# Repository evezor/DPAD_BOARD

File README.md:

# Evezor Potentiometer Board

*please note this board is has been deprecated.

This board uses the Evezor Stamp STMF405 MCU

source: https://github.com/evezor/Evezor-Stamp-STMF405

An Edge boad with two buttons, two potentiometers and 2 multiplexed led bar graphs

Evezor® and all associated marks, logos, and designs are registered trademarks and protected by copyright. Unauthorized use or reproduction of these trademarks and copyrighted materials is strictly prohibited

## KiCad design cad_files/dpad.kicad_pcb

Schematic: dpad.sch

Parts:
C1, C3: .1uF 100V; C_0805_2012Metric
C2, C5, C9, C10, C14: .1uF; C_0603_1608Metric
C4: 4.7uF; C_0805_2012Metric
C6, C7, C11, C13, C15: 22uF; C_0805_2012Metric
D1, D2: SX35_SCHOTTKY; D_SMA
D3, D4, D5, D8, D9, D10: LED; LED_0603_1608Metric
D6: SK6812MINI; LED_SK6812MINI_PLCC4_3.5x3.5mm_P1.75mm
D7: D_TVS_x2_AAC; SOT-23
J2: ftdi_conn; CONN-SH-6P-VERTICAL
J3: Conn_01x02; BOOT_JUMPER
J4, J5: Conn_01x04; JST_PH_S4B-PH-SM4-TB_1x04-1MP_P2.00mm_Horizontal
L1: 22uH; INDUCTOR_7.5X6.6_GCDA0630-220MC
R1, R3, R4, R6, R8, R9, R10: 10k; R_0603_1608Metric
R2: 82k; R_0603_1608Metric
R5, R7: 15k; R_0603_1608Metric
SW1, SW2, SW3, SW4: SW_Push; SWITCH_2x3_SMD_TACTILE_GREEN
U1: SY8401ABC; SOT-23-6
U2: AMS1117-3.3; SOT-223-3_TabPin2
U3: ESP32-WROOM-32U
U4: SWITCH_5-WAY_TACTIL_10X10; SWITCH_5WAY_10x10
U5: Trans_CAN_SN65HVD230DR; CAN-TRANS-SN65HVD230DR

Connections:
+3V3: C7.1, C9.2, C10.1, C11.1, C13.1, C14.1, C15.1, D6.4 (VDD), R3.2, R6.2, U2.2 (VO), U3.2, U5.3
/BOOT: J2.4, J3.1, U3.25
/BUTTON_A: SW4.1, U3.37
/BUTTON_B: SW3.1, U3.36
/CAN_H: D7.2, J4.2, J5.2, U5.7
/CAN_L: D7.1, J4.1, J5.1, U5.6
/CAN_RX: U3.27, U5.4
/CAN_SLP: U3.24, U5.8
/CAN_TX: U3.26, U5.1
/DPAD_DOWN: U3.12, U4.6
/DPAD_LEFT: U3.9, U4.2
/DPAD_PUSH: U3.8, U4.3
/DPAD_RIGHT: U3.11, U4.5
/DPAD_UP: U3.10, U4.4
/FUNCTION_BUTTON: R3.1, SW1.1, U3.4
/HBT_LED: D3.2 (A), U3.29
/LED_0: R4.2, U3.23
/LED_1: R8.2, U3.30
/LED_2: R9.2, U3.31
/LED_3: R10.2, U3.33
/NEO_STATUS: D6.3 (DIN), U3.28
/PWR: C3.1, C4.1, D2.1 (K), D8.2 (A), U1.4 (EN), U1.5 (VIN)
/RESET: J2.1, R6.1, SW2.1, U3.3
/RXD0: J2.3, U3.34
/TXDO: J2.2, U3.35
/VREG_OUT: C2.1, C5.1, C6.1, L1.2, R2.1, U2.3 (VI)
GND: C3.2, C4.2, C5.2, C6.2, C7.2, C9.1, C10.2, C11.2, C13.2, C14.2, C15.2, D1.2 (A), D4.1 (K), D5.1 (K), D6.2 (VSS), D7.3, D9.1 (K), D10.1 (K), J2.6, J3.2, J4.4, J5.4, R1.1, R5.1, R7.1, SW1.2, SW2.2, SW3.2, SW4.2, U1.2 (GND), U2.1 (GND), U3.1, U3.15, U3.38, U3.39, U4.1, U5.2
unnamed: C1.1, D1.1 (K), L1.1, U1.6 (SW)
unnamed: C1.2, U1.1 (CB)
unnamed: C2.2, R1.2, R2.2, U1.3 (FB)
unnamed: D3.1 (K), R5.2
unnamed: D4.2 (A), R4.1
unnamed: D5.2 (A), R8.1
unnamed: D8.1 (K), R7.2
unnamed: D9.2 (A), R9.1
unnamed: D10.2 (A), R10.1
VBUS: D2.2 (A), J2.5, J4.3, J5.3

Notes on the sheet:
EVEZOR CPU MODULE
USB C
CAN CONNECTORS
STATUS LEDS FUNCTION BUTTON BOOT/ RESET CONTACTS
VOLTAGE REGULATOR

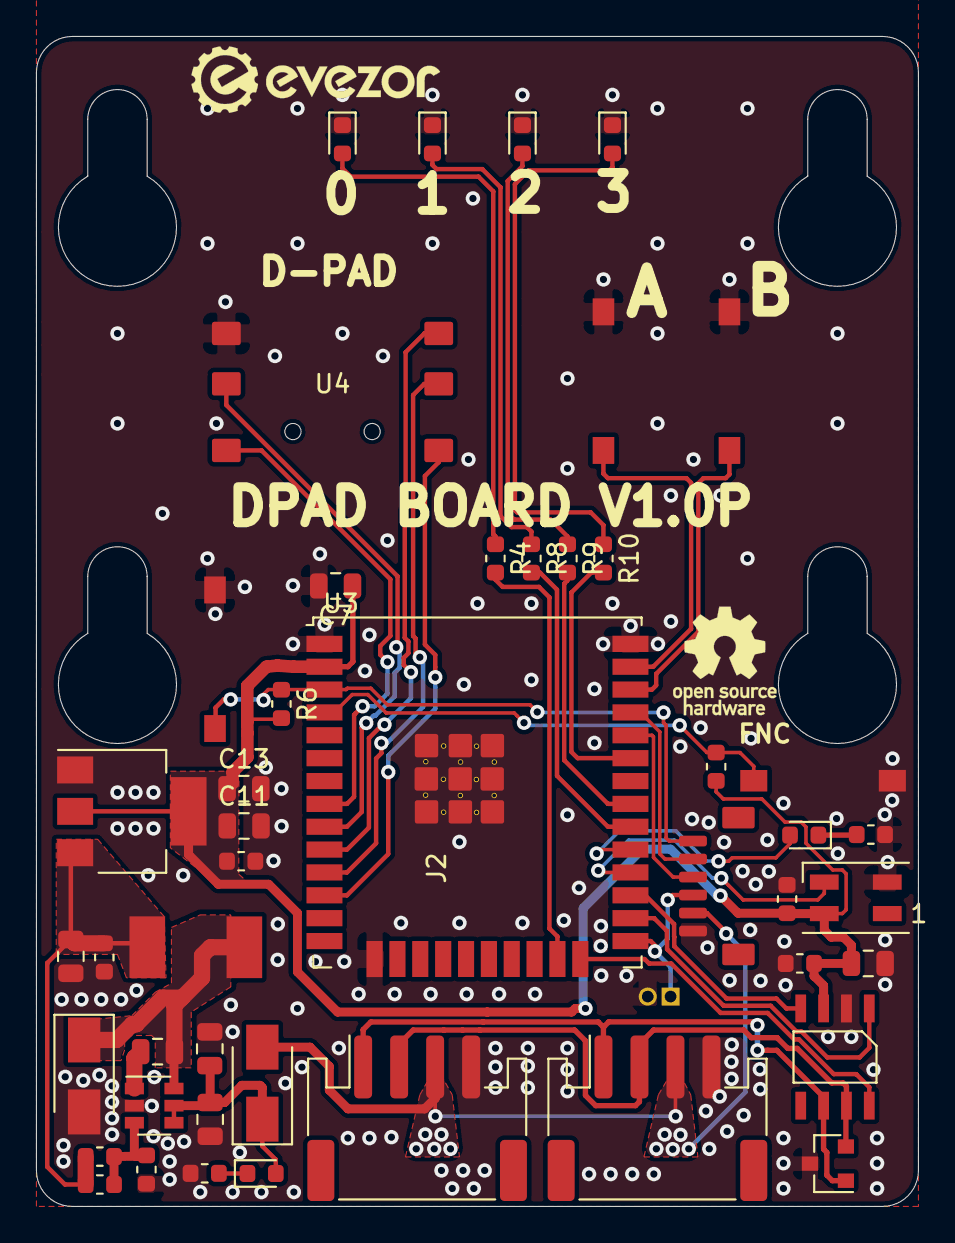
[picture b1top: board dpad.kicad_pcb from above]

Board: 2 copper layers, 49.0 x 65.0 mm, 47 parts (0 on the bottom side), 37 nets.

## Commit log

2023-09-11 Create LICENCE
2023-09-11 add pics
2023-09-11 Revert "add pics"
    This reverts commit 85ade1bbc5e8a8a479c5a3c7b0c87c73afbe33f9.
